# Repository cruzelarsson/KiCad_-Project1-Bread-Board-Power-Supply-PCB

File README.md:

This project — Simple BreadBoard Power Supply — was supported by PCBWay through their PCB prototyping sponsorship program.

PCBWay provided high-quality manufactured boards that arrived perfectly aligned and finished. The fabrication quality was excellent, with sharp silkscreen printing, clean solder masks, and precise drill accuracy.

A huge thanks to PCBWay for their support in helping bring this project to life. Their fast turnaround and reliable service made the prototyping process straightforward and efficient.

Below you will find the printed out board; the missing components will be added and uploaded soon. Thank you!

-------------------------------------------------------------------------------------------------------------------------------------------------------

3D Layout (Final Diagram)

-----------------------------------------------------------------------------------------------------------------------------------

PCB Layout with board characteristics

-----------------------------------------------------------------------------------------------------------------------------------
Schematic Layout

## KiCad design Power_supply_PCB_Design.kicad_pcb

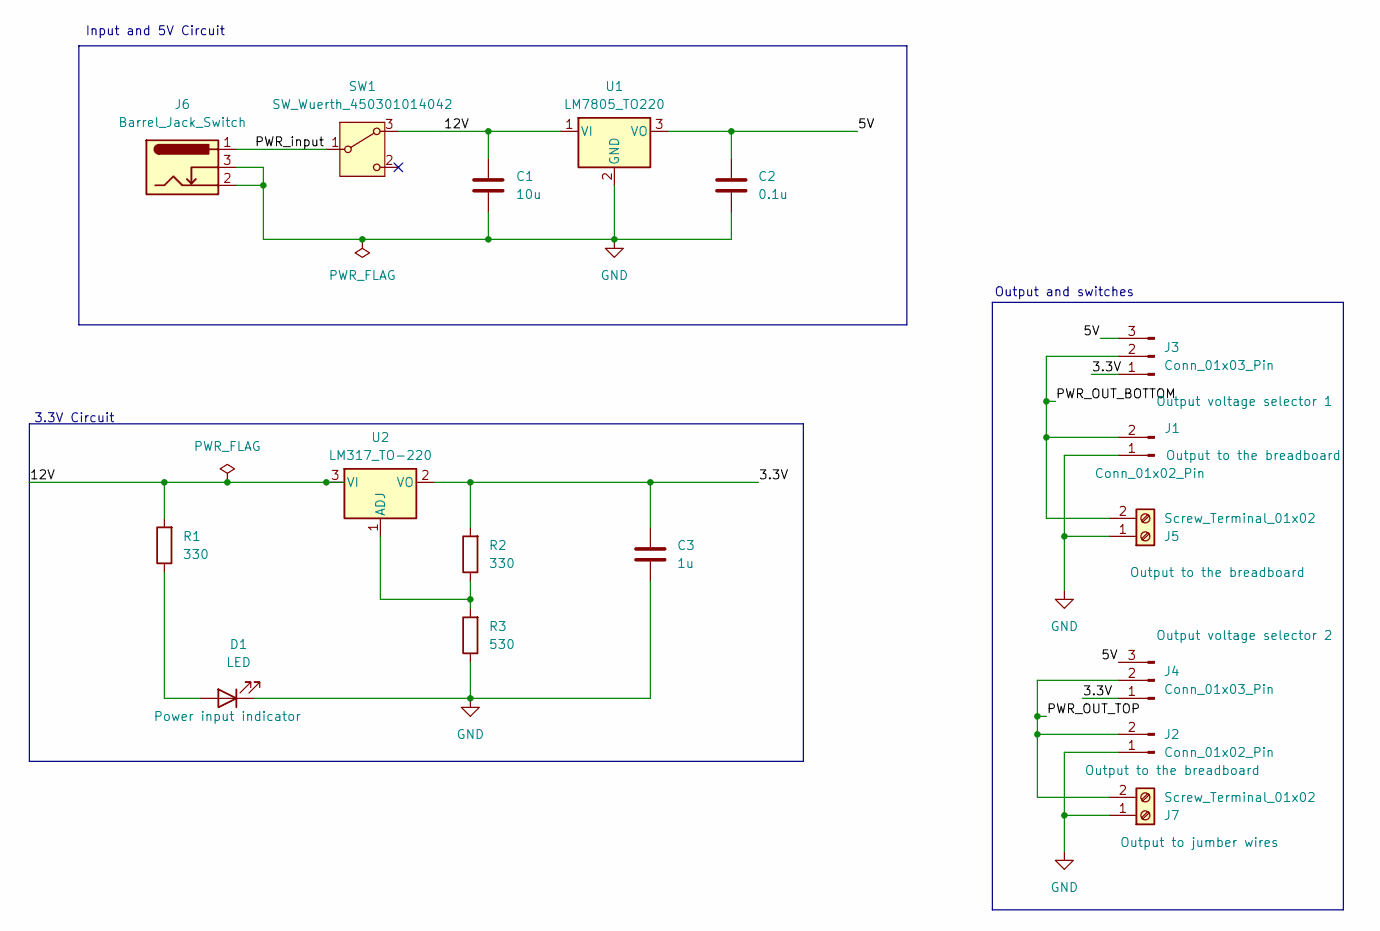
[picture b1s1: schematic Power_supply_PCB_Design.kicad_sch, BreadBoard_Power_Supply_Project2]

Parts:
C1: 10u; C_Disc_D3.0mm_W1.6mm_P2.50mm
C2: 0.1u; C_Disc_D3.0mm_W1.6mm_P2.50mm
C3: 1u; C_Disc_D3.0mm_W1.6mm_P2.50mm
D1: LED; LED_D5.0mm
J1, J2: Conn_01x02_Pin; PinHeader_1x02_P2.54mm_Vertical
J3, J4: Conn_01x03_Pin; PinHeader_1x03_P2.54mm_Vertical
J5, J7: Screw_Terminal_01x02; TerminalBlock_bornier-2_P5.08mm
J6: Barrel_Jack_Switch; BarrelJack_Horizontal
R1, R2: 330; R_Axial_DIN0204_L3.6mm_D1.6mm_P7.62mm_Horizontal
R3: 530; R_Axial_DIN0204_L3.6mm_D1.6mm_P7.62mm_Horizontal
SW1: SW_Wuerth_450301014042; SW_Slide-03_Wuerth-WS-SLTV_10x2.5x6.4_P2.54mm
U1: LM7805_TO220; TO-220-3_Vertical
U2: LM317_TO-220; TO-220-3_Vertical

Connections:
/3.3V: C3.1, J3.1, J4.1, R2.2, U2.2 (VO)
/5V: C2.1, J3.3, J4.3, U1.3 (VO)
/12V: C1.1, R1.2, SW1.3 (A), U1.1 (VI), U2.3 (VI)
/PWR_OUT_BOTTOM: J1.2, J3.2, J5.2
/PWR_OUT_TOP: J2.2, J4.2, J7.2
/PWR_input: J6.1, SW1.1 (B)
GND: C1.2, C2.2, C3.2, D1.1 (K), J1.1, J2.1, J5.1, J6.2, J6.3, J7.1, R3.1, U1.2 (GND)
unnamed: D1.2 (A), R1.1
unnamed: R2.1, R3.2, U2.1 (ADJ)

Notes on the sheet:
3.3V Circuit
Input and 5V Circuit
Output and switches

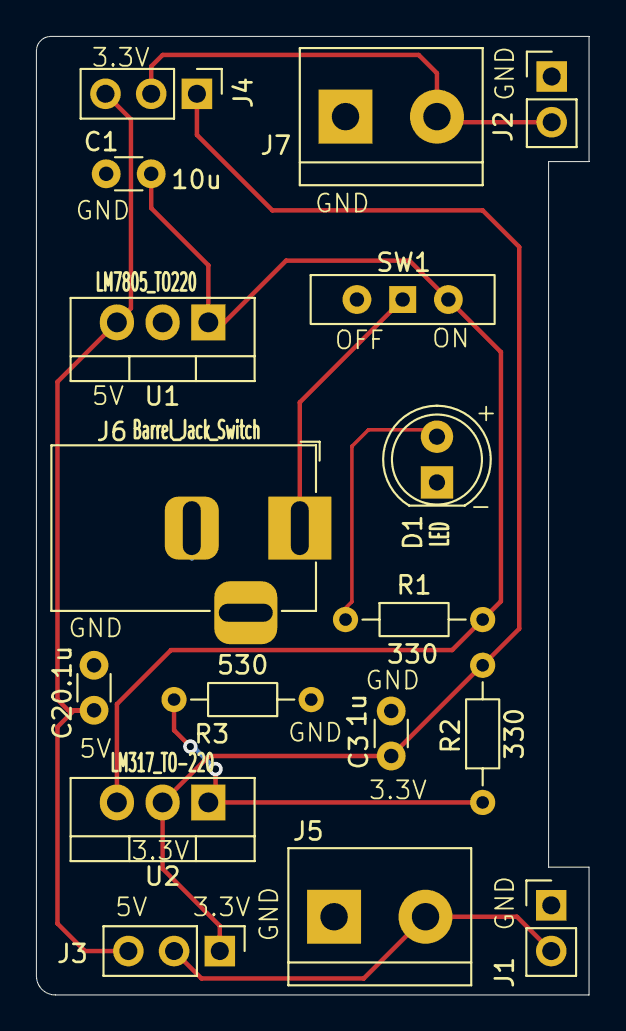
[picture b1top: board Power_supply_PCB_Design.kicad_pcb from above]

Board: 2 copper layers, 30.7 x 53.2 mm, 17 parts (0 on the bottom side), 9 nets.

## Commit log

2025-09-01 Complete project of a simple Breadboard powersupply.
2025-09-03 Additional Bug Fixes
2025-09-20 README.md
